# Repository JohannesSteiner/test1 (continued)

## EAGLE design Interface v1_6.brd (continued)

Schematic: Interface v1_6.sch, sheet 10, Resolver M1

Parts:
C1001, C1002, C1003, C1005, C1006, C1013, C1017, C1019, C1020, C1022: 100nF; C-0805"
C1004: 10u; CP-1210"
C1007, C1008: 4µ7; CP-1206"
C1009, C1010, C1014, C1018, C1021: 2µ2; C-0805"
C1011, C1012: 22pF; C-0805"
C1015, C1016: 100pF; C-0805"
C1023: NB; C-0805"
D1001, D1002, D1003, D1004: TS41480805; D-0805"
IC1001: AD2S1205; TQFP44
IC1002: TL084D; SO14
IC1003: REF3330; SOT23
IC1004: LMH6645MF; SOT23-5
L1001, L1002, L1003: 10µH; L-1206
Q1001: QUARZ10MHZ; CRYSTAL3.2X5
R1001, R1004: 0; R-0805"
R1002, R1003, R1005, R1006, R1007, R1008: 10k; R-0805"
R1009, R1010: 18k; R-0805"
R1011, R1012, R1013, R1014: 3R3; R-0805"
R1015: 3k; R-0805"
R1016: 12k; R-0805"
R1017, R1018, R1019, R1020: 2k2; R-0805"
R1021, R1022, R1023, R1024: 4R7; R-0805"
R1025: NB; R-0805"
T1001, T1003: BC846; SOT23
T1002, T1004: BC856; SOT23-BEC
TP30: TP-TH-08; TP-08

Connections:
+5V: L1001.1, L1002.1; also elsewhere on the board
+12V: L1003.1; also elsewhere on the board
AD_DIR1: IC1001.28 (DIR)
CLK_RLS1_5V: IC1001.8 (DB10/SCLK); also elsewhere on the board
CS_RLS1_5V: IC1001.2 (RD), IC1001.3 (CS); also elsewhere on the board
DOS_RLS1: IC1001.29 (DOS)
ERR_RESET_5V: R1001.1; also elsewhere on the board
ERR_RESET_RLS1: C1001.1, IC1001.33 (RESET), R1001.2
GND: C1001.2, C1002.2, C1005.2, C1007.-, C1011.1, C1012.1, IC1001.16 (DGND), IC1001.23 (DGND2), Q1001.2 (GND2), Q1001.4 (GND), R1002.1, R1004.1; also elsewhere on the board
INC_A1: IC1001.25 (A); also elsewhere on the board
INC_B1: IC1001.26 (B); also elsewhere on the board
INC_I1: IC1001.27 (NM); also elsewhere on the board
LOT_RLS1: IC1001.30 (LOT)
MISO_RLS1_5V: IC1001.7 (DB11/SO); also elsewhere on the board
unnamed: C1016.1, IC1002.2 (-IN), R1007.2, R1010.1
unnamed: C1016.2, IC1002.1 (OUT), IC1002.12 (+IN), R1010.2
unnamed: D1001.A, R1011.1
unnamed: D1001.C, D1002.A, IC1002.14 (OUT)
unnamed: D1002.C, R1012.2
unnamed: R1021.2, T1001.2 (E)
unnamed: R1022.1, T1002.E
unnamed: C1015.1, IC1002.6 (-IN), R1008.2, R1009.1
unnamed: C1015.2, IC1002.7 (OUT), IC1002.10 (+IN), R1009.2
unnamed: IC1001.34 (EXC1), R1007.1
unnamed: IC1001.35 (EXC2), R1008.1
unnamed: C1011.2, IC1001.21 (XTALOUT), Q1001.3 (C2)
unnamed: C1012.2, IC1001.22 (CLKIN), Q1001.1 (C1)
unnamed: R1012.1, R1018.2, T1002.B
unnamed: R1011.2, R1017.1, T1001.1 (B)
unnamed: D1003.A, R1013.1
unnamed: D1003.C, D1004.A, IC1002.8 (OUT)
unnamed: D1004.C, R1014.2
unnamed: R1023.2, T1003.2 (E)
unnamed: R1024.1, T1004.E
unnamed: R1014.1, R1020.2, T1004.B
unnamed: R1013.2, R1019.1, T1003.1 (B)
unnamed: C1023.2, R1025.1
unnamed: C1003.1, C1004.+, IC1001.43 (REFBYP)
unnamed: IC1001.6 (SOE), R1002.2
unnamed: IC1001.5 (RDVEL), R1003.2
unnamed: C1018.1, C1019.1, IC1003.2 (OUT), IC1004.3 (+IN)
unnamed: IC1004.4 (-IN), R1015.1, R1016.2
RLS1_+12VA: C1009.1, C1010.1, C1017.2, IC1002.4 (V+), L1003.2, R1017.2, R1019.2, T1001.3 (C), T1003.3 (C), TP30.TP
RLS1_AGND_RES: C1003.2, C1004.-, C1006.2, C1008.-, C1009.2, C1010.2, C1013.2, C1014.2, C1017.1, C1018.2, C1019.2, C1020.2, C1021.2, C1022.2, IC1001.36 (AGND), IC1001.42 (AGND2), IC1002.11 (V-), IC1003.3 (GND), IC1004.2 (-V), R1004.2, R1016.1, R1018.1, R1020.1, T1002.C, T1004.C; also elsewhere on the board
RLS1_AVDD: C1006.1, C1008.+, C1013.1, C1014.1, C1020.1, IC1001.39 (AVDD), IC1003.1 (IN), IC1004.5 (+V), L1002.2; also elsewhere on the board
RLS1_COS: IC1001.41 (COS), R1006.2; also elsewhere on the board
RLS1_COSLO: IC1001.40 (COSLO), R1006.1; also elsewhere on the board
RLS1_DVDD: C1002.1, C1005.1, C1007.+, IC1001.1 (DVDD), IC1001.17 (DVDD2), L1001.2, R1003.1
RLS1_EXC: IC1002.13 (-IN), R1021.1, R1022.2, R1025.2; also elsewhere on the board
RLS1_NEXC: C1023.1, IC1002.9 (-IN), R1023.1, R1024.2; also elsewhere on the board
RLS1_SIN: IC1001.37 (SIN), R1005.2; also elsewhere on the board
RLS1_SINLO: IC1001.38 (SINLO), R1005.1; also elsewhere on the board
RLS1_VREF: C1021.1, C1022.1, IC1002.3 (+IN), IC1002.5 (+IN), IC1004.1 (OUT), R1015.2
SAMPLE_RLS_5V: IC1001.4 (SAMPLE); also elsewhere on the board

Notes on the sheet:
VREF=3.75V
+3V

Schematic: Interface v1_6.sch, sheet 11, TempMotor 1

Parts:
C1101, C1102, C1103, C1107, C1109, C1111, C1118, C1119, C1120, C1123, C1124, C1125, C1126: NB; C-0805"
C1104, C1105, C1106: 10nF; C-0805"
C1108, C1110, C1112, C1113, C1114, C1115, C1116, C1117, C1121, C1122: 100nF; C-0805"
IC506: 74HC74D; SOIC14
IC1101, IC1102: OPA2350EA; SOIC8
IC1103, IC1104: LMC6772AIM; SOIC8
R1101, R1102, R1103, R1125, R1126, R1127, R1128, R1132, R1133, R1134, R1135, R1136, R1137, R1138, R1140: 0; R-0805"
R1104, R1105, R1106, R1107, R1109, R1111, R1139: 10k; R-0805"
R1108, R1110, R1112: 1k; R-0805"
R1113, R1114, R1115, R1116, R1117, R1118, R1119, R1120, R1121, R1122, R1123, R1124: 22k; R-0805"
R1129, R1130, R1131: NB; R-0805"
TP31, TP32, TP33, TP34, TP35, TP36, TP37: TP-TH-08; TP-08
X1101: MINIBRIDGE12-GERADE

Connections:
+3V3: C1121.1, C1122.1, IC506.13 (!R), IC1103.8 (V+), IC1104.8 (V+), R1139.2; also elsewhere on the board
ERR_RESET: IC506.11 (CLK); also elsewhere on the board
ERR_T1_UNLATCHED: R1136.2, R1137.2, R1138.2, R1139.1, R1140.1
ERR_T_MOTOR1: IC506.8 (!Q); also elsewhere on the board
GND: C1121.2, C1122.2, C1126.2, IC506.12 (D), IC1103.4 (V-), IC1104.4 (V-), IC1104.5 (+IN), IC1104.6 (-IN); also elsewhere on the board
unnamed: IC1103.1 (OUT), R1136.1
unnamed: C1104.1, R1107.1, R1108.2, R1113.2
unnamed: C1105.1, R1109.1, R1110.2, R1115.2
unnamed: C1106.2, R1111.1, R1112.2, R1117.2
unnamed: IC1103.7 (OUT), R1137.1
unnamed: IC1104.1 (OUT), R1138.1
unnamed: C1102.1, R1102.1, R1105.1, R1116.1, TP32.TP
unnamed: C1101.1, R1101.1, R1104.1, R1114.1, TP31.TP
unnamed: C1109.1, C1115.1, IC1101.2 (-IN), R1113.1, R1122.2
unnamed: C1109.2, C1110.1, IC1101.3 (+IN), R1114.2, R1119.2
unnamed: C1111.2, C1112.1, IC1101.6 (-IN), R1116.2, R1120.2
unnamed: C1103.1, R1103.1, R1106.1, R1118.1, TP33.TP
unnamed: C1107.1, C1117.1, IC1102.2 (-IN), R1117.1, R1124.2
unnamed: C1107.2, C1108.1, IC1102.3 (+IN), R1118.2, R1121.2
unnamed: C1111.1, C1116.1, IC1101.5 (+IN), R1115.1, R1123.2
unnamed: C1126.1, IC506.10 (!S), R1140.2
unnamed: C1123.1, IC1103.3 (+IN), R1133.1
unnamed: C1124.1, IC1103.5 (+IN), R1134.1
unnamed: C1125.1, IC1104.3 (+IN), R1135.1
RLS1_AGND_RES: C1101.2, C1102.2, C1103.2, C1104.2, C1105.2, C1106.1, C1108.2, C1110.2, C1112.2, C1113.2, C1114.2, C1118.2, C1119.2, C1120.2, C1123.2, C1124.2, C1125.2, IC1101.4 (V-), IC1102.4 (V-), IC1102.5 (+IN), IC1102.6 (-IN), R1108.1, R1110.1, R1112.1, R1119.1, R1120.1, R1121.1, R1128.2, R1129.1, R1130.1, R1131.1, X1101.2, X1101.4, X1101.6; also elsewhere on the board
RLS1_AVDD: C1113.1, C1114.1, IC1101.8 (V+), IC1102.8 (V+), R1104.2, R1105.2, R1106.2, R1107.2, R1109.2, R1111.2, R1132.1; also elsewhere on the board
RLS1_COS: X1101.10; also elsewhere on the board
RLS1_COSLO: X1101.9; also elsewhere on the board
RLS1_EXC: X1101.12; also elsewhere on the board
RLS1_NEXC: X1101.11; also elsewhere on the board
RLS1_SIN: X1101.8; also elsewhere on the board
RLS1_SINLO: X1101.7; also elsewhere on the board
TEMP_MAX: R1128.1, R1132.2, R1133.2, R1134.2, R1135.2, TP37.TP
TM11+: R1101.2, X1101.1
TM12+: R1102.2, X1101.3
TM13+: R1103.2, X1101.5
T_M1-1_A: C1118.1, IC1103.2 (-IN), R1125.2, R1129.2, TP34.TP
T_M1-2_A: C1119.1, IC1103.6 (-IN), R1126.2, R1130.2, TP35.TP
T_M1-3_A: C1120.1, IC1104.2 (-IN), R1127.2, R1131.2, TP36.TP
T_MOT1-1: C1115.2, IC1101.1 (OUT), R1122.1, R1125.1; also elsewhere on the board
T_MOT1-2: C1116.2, IC1101.7 (OUT), R1123.1, R1126.1; also elsewhere on the board
T_MOT1-3: C1117.2, IC1102.1 (OUT), R1124.1, R1127.1; also elsewhere on the board

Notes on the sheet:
fg = 7200Hz
ERR

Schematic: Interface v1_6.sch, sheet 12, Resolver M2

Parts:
C1201, C1202, C1203, C1205, C1206, C1213, C1217, C1219, C1220, C1222: 100nF; C-0805"
C1204: 10µ; CP-1210"
C1207, C1208: 4µ7; CP-1206"
C1209, C1210, C1214, C1218, C1221: 2µ2; C-0805"
C1211, C1212: 22pF; C-0805"
C1215, C1216: 100pF; C-0805"
C1223: NB; C-0805"
D1201, D1202, D1203, D1204: TS41480805; D-0805"
IC1201: AD2S1205; TQFP44
IC1202: TL084D; SO14
IC1203: REF3330; SOT23
IC1204: LMH6645MF; SOT23-5
L1201, L1202, L1203: 10µH; L-1206
Q1201: QUARZ10MHZ; CRYSTAL3.2X5
R1201, R1204: 0; R-0805"
R1202, R1203, R1205, R1206, R1207, R1208: 10k; R-0805"
R1209, R1210: 18k; R-0805"
R1211, R1212, R1213, R1214: 3R3; R-0805"
R1215: 3k; R-0805"
R1216: 12k; R-0805"
R1217, R1218, R1219, R1220: 2k2; R-0805"
R1221, R1222, R1223, R1224: 4R7; R-0805"
R1225: NB; R-0805"
T1201, T1203: BC846; SOT23
T1202, T1204: BC856; SOT23-BEC
TP38: TP-TH-08; TP-08

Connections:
+5V: L1201.1, L1202.1; also elsewhere on the board
+12V: L1203.1; also elsewhere on the board
AD_DIR2: IC1201.28 (DIR)
CLK_RLS2_5V: IC1201.8 (DB10/SCLK); also elsewhere on the board
CS_RLS2_5V: IC1201.2 (RD), IC1201.3 (CS); also elsewhere on the board
DOS_RLS2: IC1201.29 (DOS)
ERR_RESET_5V: R1201.1; also elsewhere on the board
ERR_RESET_RLS2: C1201.1, IC1201.33 (RESET), R1201.2
GND: C1201.2, C1202.2, C1205.2, C1207.-, C1211.1, C1212.1, IC1201.16 (DGND), IC1201.23 (DGND2), Q1201.2 (GND2), Q1201.4 (GND), R1203.1, R1204.1; also elsewhere on the board
INC_A2: IC1201.25 (A); also elsewhere on the board
INC_B2: IC1201.26 (B); also elsewhere on the board
INC_I2: IC1201.27 (NM); also elsewhere on the board
LOT_RLS2: IC1201.30 (LOT)
MISO_RLS2_5V: IC1201.7 (DB11/SO); also elsewhere on the board
unnamed: C1216.1, IC1202.2 (-IN), R1207.2, R1210.1
unnamed: C1216.2, IC1202.1 (OUT), IC1202.12 (+IN), R1210.2
unnamed: D1201.A, R1211.1
unnamed: D1201.C, D1202.A, IC1202.14 (OUT)
unnamed: D1202.C, R1212.2
unnamed: R1221.2, T1201.2 (E)
unnamed: R1222.1, T1202.E
unnamed: C1215.1, IC1202.6 (-IN), R1208.2, R1209.1
unnamed: C1215.2, IC1202.7 (OUT), IC1202.10 (+IN), R1209.2
unnamed: IC1201.34 (EXC1), R1207.1
unnamed: IC1201.35 (EXC2), R1208.1
unnamed: C1211.2, IC1201.21 (XTALOUT), Q1201.3 (C2)
unnamed: C1212.2, IC1201.22 (CLKIN), Q1201.1 (C1)
unnamed: R1212.1, R1218.2, T1202.B
unnamed: R1211.2, R1217.1, T1201.1 (B)
unnamed: D1203.A, R1213.1
unnamed: D1203.C, D1204.A, IC1202.8 (OUT)
unnamed: D1204.C, R1214.2
unnamed: R1223.2, T1203.2 (E)
unnamed: R1224.1, T1204.E
unnamed: R1214.1, R1220.2, T1204.B
unnamed: R1213.2, R1219.1, T1203.1 (B)
unnamed: C1223.2, R1225.1
unnamed: C1203.1, C1204.+, IC1201.43 (REFBYP)
unnamed: IC1201.6 (SOE), R1203.2
unnamed: IC1201.5 (RDVEL), R1202.2
unnamed: C1218.1, C1219.1, IC1203.2 (OUT), IC1204.3 (+IN)
unnamed: IC1204.4 (-IN), R1215.1, R1216.2
RLS2_+12VA: C1209.1, C1210.1, C1217.2, IC1202.4 (V+), L1203.2, R1217.2, R1219.2, T1201.3 (C), T1203.3 (C)
RLS2_AGND_RES: C1203.2, C1204.-, C1206.2, C1208.-, C1209.2, C1210.2, C1213.2, C1214.2, C1217.1, C1218.2, C1219.2, C1220.2, C1221.2, C1222.2, IC1201.36 (AGND), IC1201.42 (AGND2), IC1202.11 (V-), IC1203.3 (GND), IC1204.2 (-V), R1204.2, R1216.1, R1218.1, R1220.1, T1202.C, T1204.C; also elsewhere on the board
RLS2_AVDD: C1206.1, C1208.+, C1213.1, C1214.1, C1220.1, IC1201.39 (AVDD), IC1203.1 (IN), IC1204.5 (+V), L1202.2; also elsewhere on the board
RLS2_COS: IC1201.41 (COS), R1206.2; also elsewhere on the board
RLS2_COSLO: IC1201.40 (COSLO), R1206.1; also elsewhere on the board
RLS2_DVDD: C1202.1, C1205.1, C1207.+, IC1201.1 (DVDD), IC1201.17 (DVDD2), L1201.2, R1202.1
RLS2_EXC: IC1202.13 (-IN), R1221.1, R1222.2, R1225.2; also elsewhere on the board
RLS2_NEXC: C1223.1, IC1202.9 (-IN), R1223.1, R1224.2; also elsewhere on the board
RLS2_SIN: IC1201.37 (SIN), R1205.2; also elsewhere on the board
RLS2_SINLO: IC1201.38 (SINLO), R1205.1; also elsewhere on the board
RLS2_VREF: C1221.1, C1222.1, IC1202.3 (+IN), IC1202.5 (+IN), IC1204.1 (OUT), R1215.2, TP38.TP
SAMPLE_RLS_5V: IC1201.4 (SAMPLE); also elsewhere on the board

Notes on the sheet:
VREF=3.75V
+3V

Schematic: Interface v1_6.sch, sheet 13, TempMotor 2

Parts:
C1301, C1302, C1303, C1318, C1319, C1320, C1323, C1324, C1325, C1326: NB; C-0805"
C1304, C1305, C1306, C1307, C1309, C1311: 10nF; C-0805"
C1308, C1310, C1312, C1313, C1314, C1315, C1316, C1317, C1321, C1322: 100nF; C-0805"
IC606: 74HC74D; SOIC14
IC1301, IC1302: OPA2350EA; SOIC8
IC1303, IC1304: LMC6772AIM; SOIC8
R1301, R1302, R1303, R1325, R1326, R1327, R1333, R1334, R1335, R1336, R1337, R1338, R1340: 0; R-0805"
R1304, R1305, R1306, R1307, R1309, R1311, R1339: 10k; R-0805"
R1308, R1310, R1312: 1k; R-0805"
R1313, R1314, R1315, R1316, R1317, R1318, R1319, R1320, R1321, R1322, R1323, R1324: 22k; R-0805"
R1328, R1332: R-0805"
R1329, R1330, R1331: NB; R-0805"
TP39, TP40, TP41, TP42, TP43, TP44, TP45: TP-TH-08; TP-08
TP46: TP-TH-12; TP-12
X1301: MINIBRIDGE12-GERADE

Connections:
+3V3: C1321.1, C1322.1, IC606.13 (!R), IC1303.8 (V+), IC1304.8 (V+), R1339.2; also elsewhere on the board
+5V: R1304.2, R1305.2, R1306.2, R1307.2, R1309.2, R1311.2; also elsewhere on the board
ERR_RESET: IC606.11 (CLK); also elsewhere on the board
ERR_T2_UNLATCHED: R1336.2, R1337.2, R1338.2, R1339.1, R1340.1
ERR_T_MOTOR2: IC606.8 (!Q); also elsewhere on the board
GND: C1321.2, C1322.2, C1326.2, IC606.12 (D), IC1303.4 (V-), IC1304.4 (V-), IC1304.5 (+IN), IC1304.6 (-IN); also elsewhere on the board
unnamed: IC1303.1 (OUT), R1336.1
unnamed: IC1303.7 (OUT), R1337.1
unnamed: IC1304.1 (OUT), R1338.1
unnamed: C1301.1, R1301.1, R1304.1, R1314.1, TP39.TP
unnamed: C1307.1, C1315.1, IC1301.2 (-IN), R1313.1, R1322.2
unnamed: C1307.2, C1308.1, IC1301.3 (+IN), R1314.2, R1319.2
unnamed: C1302.1, R1302.1, R1305.1, R1316.1, TP40.TP
unnamed: C1309.1, C1310.1, IC1301.6 (-IN), R1316.2, R1320.2
unnamed: C1303.1, R1303.1, R1306.1, R1318.1, TP41.TP
unnamed: C1311.2, C1317.1, IC1302.2 (-IN), R1317.1, R1324.2
unnamed: C1311.1, C1312.1, IC1302.3 (+IN), R1318.2, R1321.2
unnamed: C1323.1, IC1303.3 (+IN), R1333.1
unnamed: C1324.1, IC1303.5 (+IN), R1334.1
unnamed: C1325.1, IC1304.3 (+IN), R1335.1
unnamed: C1309.2, C1316.1, IC1301.5 (+IN), R1315.1, R1323.2
unnamed: C1304.1, R1307.1, R1308.2, R1313.2
unnamed: C1305.1, R1309.1, R1310.2, R1315.2
unnamed: C1306.2, R1311.1, R1312.2, R1317.2
unnamed: C1326.1, IC606.10 (!S), R1340.2
RLS2_AGND_RES: C1301.2, C1302.2, C1303.2, C1304.2, C1305.2, C1306.1, C1308.2, C1310.2, C1312.2, C1313.2, C1314.2, C1318.2, C1319.2, C1320.2, C1323.2, C1324.2, C1325.2, IC1301.4 (V-), IC1302.4 (V-), IC1302.5 (+IN), IC1302.6 (-IN), R1308.1, R1310.1, R1312.1, R1319.1, R1320.1, R1321.1, R1328.2, R1329.1, R1330.1, R1331.1, TP46.TP, X1301.2, X1301.4, X1301.6; also elsewhere on the board
RLS2_AVDD: C1313.1, C1314.1, IC1301.8 (V+), IC1302.8 (V+), R1332.1; also elsewhere on the board
RLS2_COS: X1301.10; also elsewhere on the board
RLS2_COSLO: X1301.9; also elsewhere on the board
RLS2_EXC: X1301.12; also elsewhere on the board
RLS2_NEXC: X1301.11; also elsewhere on the board
RLS2_SIN: X1301.8; also elsewhere on the board
RLS2_SINLO: X1301.7; also elsewhere on the board
TEMP_MAX1: R1328.1, R1332.2, R1333.2, R1334.2, R1335.2, TP45.TP
TM21+: R1301.2, X1301.1
TM22+: R1302.2, X1301.3
TM23+: R1303.2, X1301.5
T_M1-1_A1: C1318.1, IC1303.2 (-IN), R1325.2, R1329.2, TP42.TP
T_M1-2_A1: C1319.1, IC1303.6 (-IN), R1326.2, R1330.2, TP43.TP
T_M1-3_A1: C1320.1, IC1304.2 (-IN), R1327.2, R1331.2, TP44.TP
T_MOT2-1: C1315.2, IC1301.1 (OUT), R1322.1, R1325.1; also elsewhere on the board
T_MOT2-2: C1316.2, IC1301.7 (OUT), R1323.1, R1326.1; also elsewhere on the board
T_MOT2-3: C1317.2, IC1302.1 (OUT), R1324.1, R1327.1; also elsewhere on the board

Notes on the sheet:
fg = 7200Hz
ERR

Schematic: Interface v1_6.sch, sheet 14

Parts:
C1401, C1402, C1403, C1404: C-0805"
U1401, U1402, U1403, U1404, U1405, U1406, U1407, U1408: TMV2
X1401: M1; 44769-2201_EUGEN
X1402: M2; 44769-2201_EUGEN
Z1401, Z1403, Z1405, Z1407, Z1409, Z1411, Z1413, Z1415: 20V; D-SOD123W
Z1402, Z1404, Z1406, Z1408, Z1410, Z1412, Z1414, Z1416: 12V; D-SOD123W

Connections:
+12V_IGBT: C1401.1, C1402.1, C1403.1, C1404.1, U1401.1 (+VIN), U1402.1 (+VIN), U1403.1 (+VIN), U1404.1 (+VIN), U1405.1 (+VIN), U1406.1 (+VIN), U1407.1 (+VIN), U1408.1 (+VIN); also elsewhere on the board
GND: C1401.2, C1402.2, C1403.2, C1404.2, U1401.2 (-VIN), U1402.2 (-VIN), U1403.2 (-VIN), U1404.2 (-VIN), U1405.2 (-VIN), U1406.2 (-VIN), U1407.2 (-VIN), U1408.2 (-VIN); also elsewhere on the board
GND_1B: U1404.6 (COMMON), X1401.P21 (21), Z1407.A (A1), Z1408.C (C1)
GND_U1T: U1401.6 (COMMON), X1401.P1 (1), Z1401.A (A1), Z1402.C (C1)
GND_U2T: U1405.6 (COMMON), X1402.P1 (1), Z1409.A (A1), Z1410.C (C1)
GND_V1T: U1402.6 (COMMON), X1401.P7 (7), Z1403.A (A1), Z1404.C (C1)
GND_W1T: U1403.6 (COMMON), X1401.P13 (13), Z1405.A (A1), Z1406.C (C1)
unnamed: U1406.7 (+VOUT), X1402.P8 (8), Z1411.C (C1)
unnamed: U1406.6 (COMMON), X1402.P7 (7), Z1411.A (A1), Z1412.C (C1)
unnamed: U1406.5 (-VOUT), X1402.P9 (9), Z1412.A (A1)
unnamed: U1407.7 (+VOUT), X1402.P14 (14), Z1413.C (C1)
unnamed: U1407.6 (COMMON), X1402.P13 (13), Z1413.A (A1), Z1414.C (C1)
unnamed: U1407.5 (-VOUT), X1402.P15 (15), Z1414.A (A1)
unnamed: U1408.7 (+VOUT), X1402.P19 (19), Z1415.C (C1)
unnamed: U1408.6 (COMMON), X1402.P21 (21), Z1415.A (A1), Z1416.C (C1)
unnamed: U1408.5 (-VOUT), X1402.P20 (20), Z1416.A (A1)
VCC_1B: U1404.7 (+VOUT), X1401.P19 (19), Z1407.C (C1)
VCC_U1T: U1401.7 (+VOUT), X1401.P4 (4), Z1401.C (C1)
VCC_U2T: U1405.7 (+VOUT), X1402.P4 (4), Z1409.C (C1)
VCC_V1T: U1402.7 (+VOUT), X1401.P8 (8), Z1403.C (C1)
VCC_W1T: U1403.7 (+VOUT), X1401.P14 (14), Z1405.C (C1)
VSS_1B: U1404.5 (-VOUT), X1401.P20 (20), Z1408.A (A1)
VSS_U1T: U1401.5 (-VOUT), X1401.P3 (3), Z1402.A (A1)
VSS_U2T: U1405.5 (-VOUT), X1402.P3 (3), Z1410.A (A1)
VSS_V1T: U1402.5 (-VOUT), X1401.P9 (9), Z1404.A (A1)
VSS_W1T: U1403.5 (-VOUT), X1401.P15 (15), Z1406.A (A1)

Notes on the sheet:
Power Supply Gate Driver

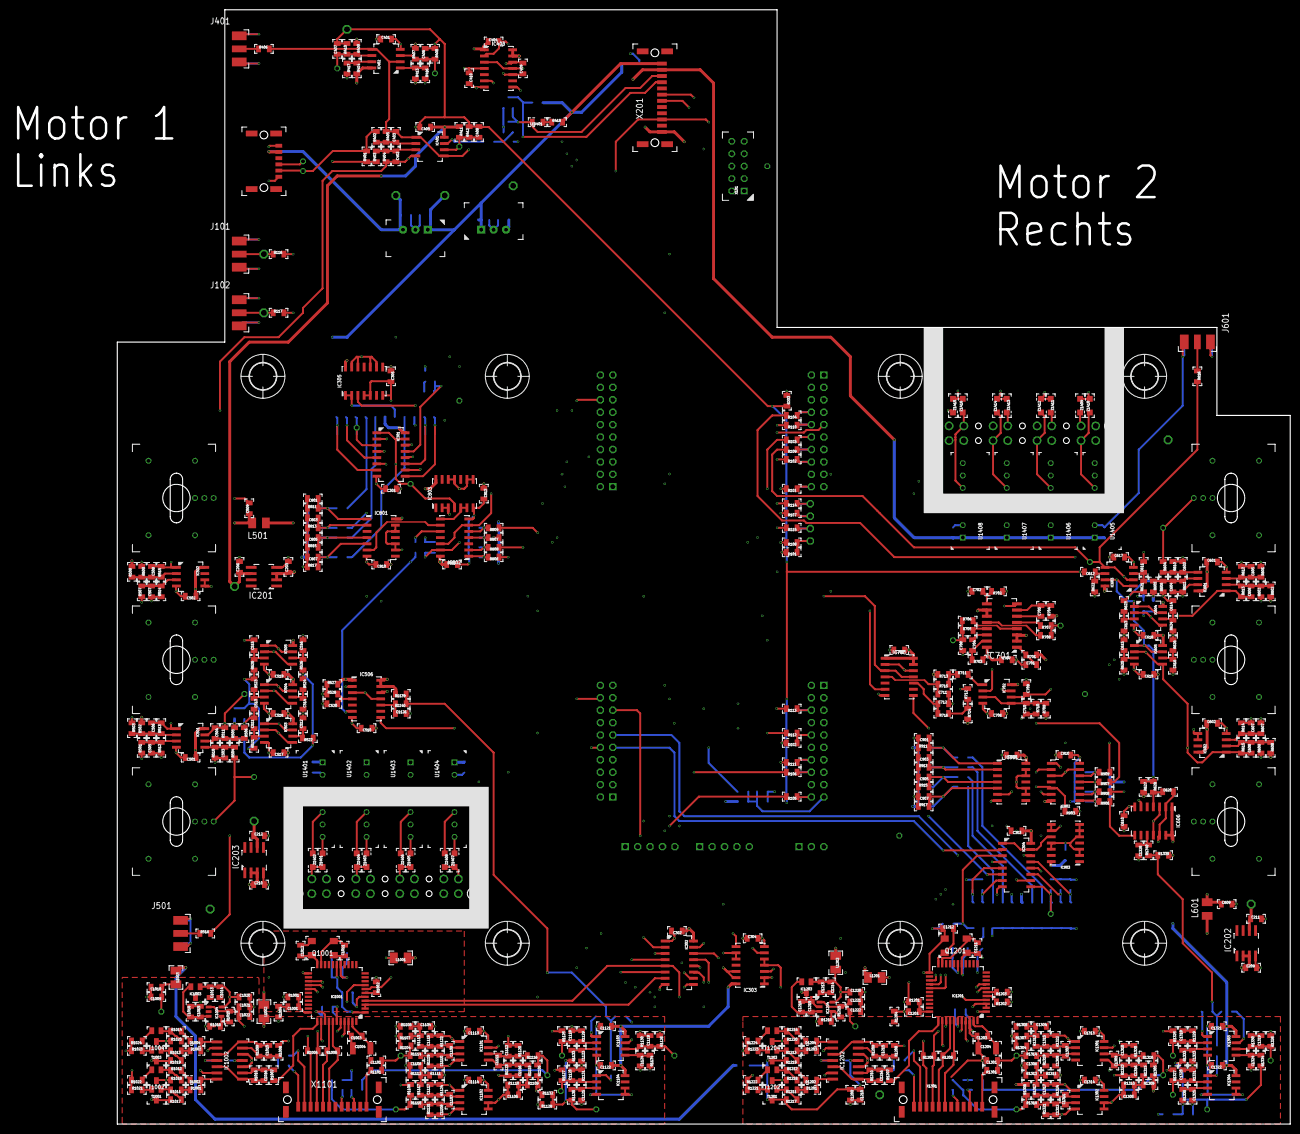
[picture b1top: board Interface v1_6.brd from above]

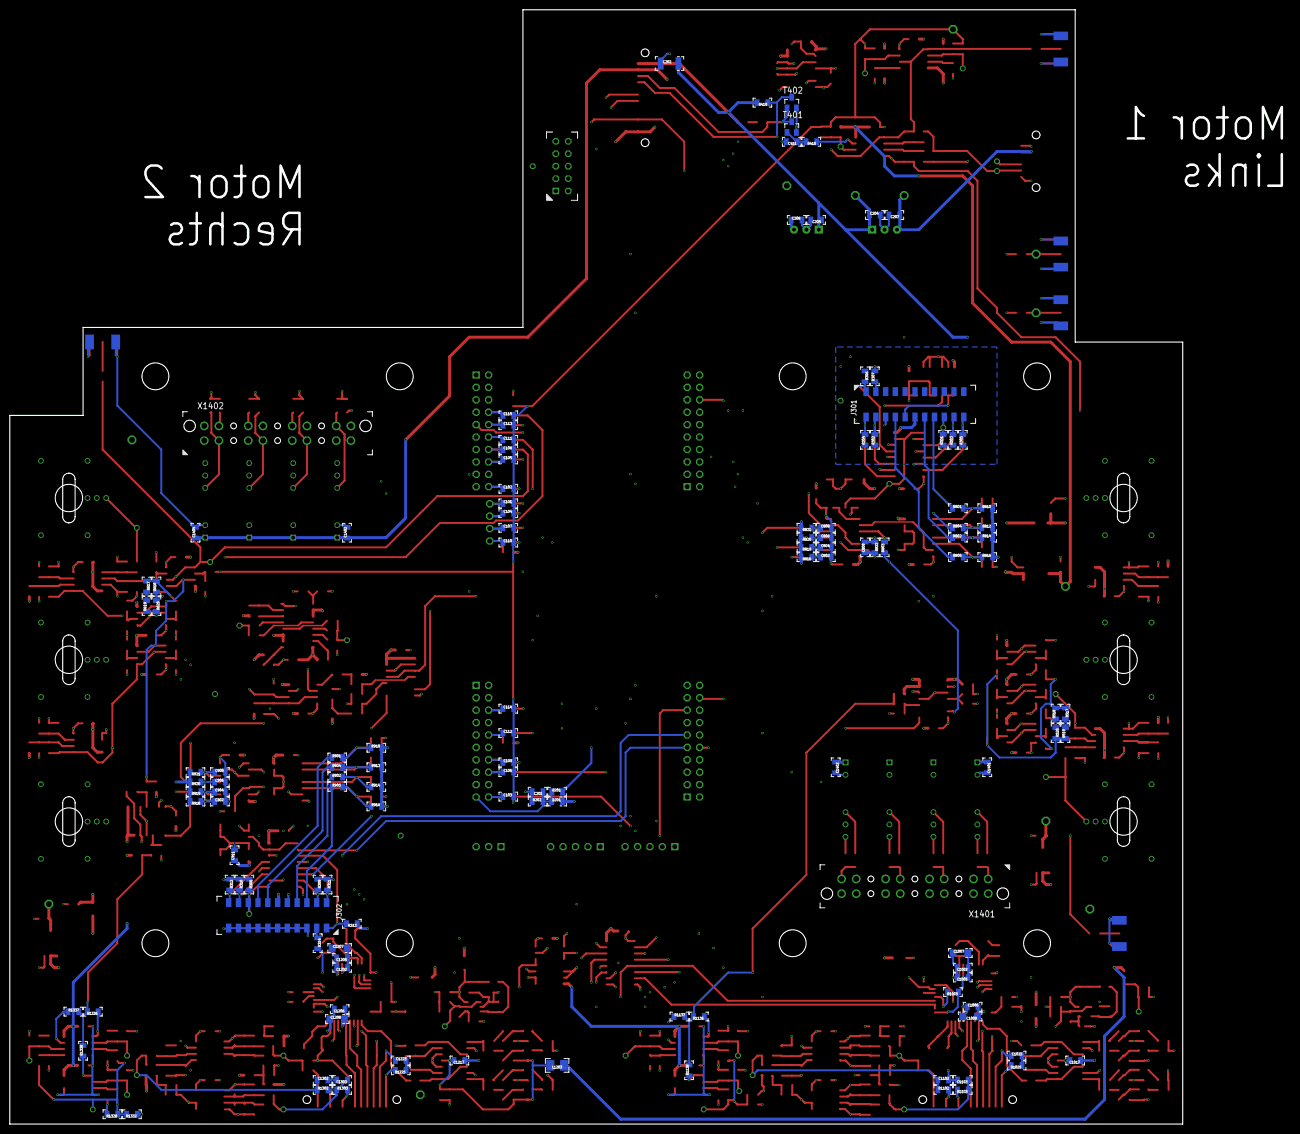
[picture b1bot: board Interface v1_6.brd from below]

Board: 6 copper layers, 262.0 x 228.0 mm, 699 parts (129 on the bottom side), 383 nets.

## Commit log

2018-01-12 Added some mistakes
